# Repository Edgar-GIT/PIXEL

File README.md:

# PIXEL

**Sistema inteligente de assistência à identificação de cores** — Prova de Aptidão Profissional (PAP) — apresentação de introdução.

O PIXEL é um pequeno módulo eletrónico destacável, para acoplar a praticamente qualquer par de óculos. Ajuda pessoas com daltonismo (deficiência da visão cromática) a identificar cores e a interpretar informação visual. Tem dois modos:

- **Traffic Mode** — analisa automaticamente as imagens da câmara, deteta semáforos e o seu estado, e emite um aviso sonoro quando há uma mudança confirmada. Funciona sem comandos de voz nem botões.
- **Free Vision** — responde a perguntas por voz ("PIXEL, qual é a cor do objeto à minha frente?"), usando visão computacional e IA (Gemini).

> ⚠️ O PIXEL é um **protótipo experimental de assistência**. Não é um sistema certificado de segurança rodoviária e não decide se o utilizador pode atravessar. O utilizador deve continuar a observar o ambiente e a sinalização.

## Arquitetura

```
Óculos PIXEL (XIAO ESP32-S3 Sense, C++)  ──BLE + Wi-Fi──►  App Android (Kotlin + OpenCV)  ──HTTPS──►  Backend (Go)  ──►  Gemini API
   câmara · microfone · altifalante                          modos · deteções · voz                     API · encaminhamento
```

| Tecnologia | Responsabilidade |
|---|---|
| C++ | Firmware do ESP32-S3 |
| Kotlin | Aplicação Android |
| Go | Backend e API |
| OpenCV | Visão computacional (no telemóvel) |
| Gemini API | Interpretação de imagens e linguagem natural |
| KiCad 10 | Esquema, PCB e modelos 3D |

## Estado atual (rev. 0.1 — 22/11/2026)

| Componente | Estado |
|---|---|
| Hardware — protótipo em meia placa perfurada 35 × 50 mm (KiCad) | ✅ Desenhado; ERC/DRC sem erros; peças iniciais + divisor de tensão da bateria |
| Hardware — PCB final (KiCad) | ✅ Desenhado; ERC/DRC sem erros; **ainda não fabricado nem testado** |
| Documentação de hardware e orçamento | ✅ [`hardware/PIXEL_HARDWARE.md`](hardware/PIXEL_HARDWARE.md) · [`hardware/PIXEL_BOM.csv`](hardware/PIXEL_BOM.csv) |
| Apresentação PAP | ✅ `apresentacoes/PIXEL_PAP.pptx` + guião `apresentacoes/PIXEL_GUIAO.md` |
| Firmware, aplicação Android, backend | ⏳ Por desenvolver (fora do âmbito desta fase) |

## Estrutura do repositório

```
PIXEL/
├── README.md
├── logo.png                         ← logótipo original
├── apresentacoes/
│   ├── PIXEL_PAP.pptx               ← apresentação da PAP (editável)
│   ├── PIXEL_GUIAO.md               ← o que dizer em cada diapositivo
│   ├── assets/                      ← logótipo transparente, renders KiCad, imagens dos slides
│   └── exports/                     ← PDF da apresentação
├── hardware/
│   ├── PIXEL_HARDWARE.md            ← arquitetura, BOM, ligações, alimentação, comunicação, pendentes
│   ├── PIXEL_BOM.csv                ← lista de materiais com preços e fontes
│   ├── datasheets/                  ← datasheets consultados
│   ├── renders/                     ← protótipo (PIXEL_PROTO_*), layout e 3D da PCB final, esquemas (PDF/PNG)
│   └── kicad/
│       ├── libs/                    ← bibliotecas do projeto (Seeed OPL + modelos 3D)
│       ├── PIXEL/                   ← PCB final (54 × 24 mm) + fabrication/ (Gerbers)
│       ├── PIXEL_DEV/               ← PCB final em vista de layout (mesmo esquema)
│       ├── PIXEL_PROTO/             ← protótipo: layout final (meia placa 35 × 50 mm)
│       ├── PIXEL_PROTO_DEV/         ← protótipo: vista de ligações 70 × 50 mm
│       └── reports/                 ← relatórios ERC/DRC
└── relatorios/                      ← relatório da PAP (outra fase)
```

## Abrir os projetos KiCad

1. Instalar o **KiCad 10** (os ficheiros foram criados e verificados com o KiCad 10.0.8).
2. Abrir `hardware/kicad/PIXEL_PROTO/PIXEL_PROTO.kicad_pro` (protótipo; vista de ligações em `PIXEL_PROTO_DEV`), `hardware/kicad/PIXEL/PIXEL.kicad_pro` (PCB final) ou `hardware/kicad/PIXEL_DEV/PIXEL_DEV.kicad_pro` (layout da PCB final).
3. As bibliotecas do projeto carregam-se automaticamente, com caminhos relativos para `hardware/kicad/libs/`.

Verificação pela linha de comandos:

```bash
cd hardware/kicad/PIXEL
kicad-cli sch erc PIXEL.kicad_sch
kicad-cli pcb drc --schematic-parity PIXEL.kicad_pcb
```

## Créditos e licenças

- Símbolo, footprint e esquema de referência do XIAO ESP32-S3: [Seeed Studio OPL KiCad Library](https://github.com/Seeed-Studio/OPL_Kicad_Library) (CC BY-SA 4.0).
- Modelo 3D do XIAO ESP32-S3 Sense: Seeed Studio (pacote oficial da wiki).
- Restantes símbolos, footprints e modelos 3D: bibliotecas oficiais do KiCad.

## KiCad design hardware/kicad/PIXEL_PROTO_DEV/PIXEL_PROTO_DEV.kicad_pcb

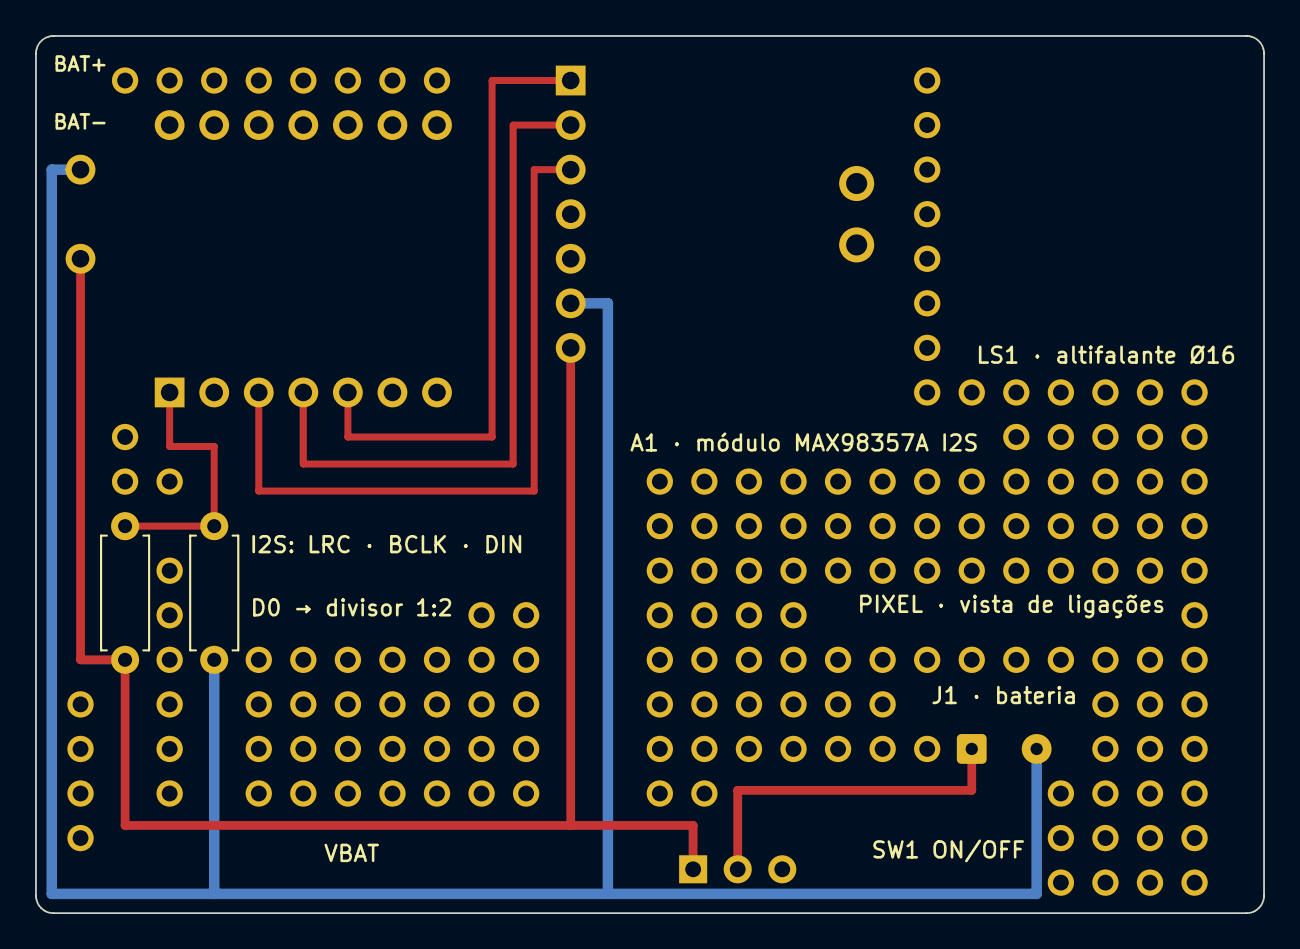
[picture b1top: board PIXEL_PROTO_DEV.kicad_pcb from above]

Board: 2 copper layers, 70.0 x 50.0 mm, 9 parts (1 on the bottom side), 7 nets.

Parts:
A1: Módulo MAX98357A I2S; Adafruit_MAX98357A_3006
J1: Fios da bateria; SolderWire-0.127sqmm_1x02_P3.7mm_D0.48mm_OD1mm
MECH1: Speaker_LD-SP-U15.5_Virtual
MECH2: LiPo_EasyLander_103040_Virtual
PERF1: Placa perfurada 70x50 mm (vista de ligações); Perfboard_70x50_P2.54mm
R1, R2: 100k; R_Axial_DIN0207_L6.3mm_D2.5mm_P7.62mm_Horizontal
SW1: ESP1010 0,5 A (ON/OFF); SW_Slide_SPDT_ESP1010_P2.54mm
U1: XIAO ESP32-S3 Sense; XIAO-ESP32-S3-Sense_Headers_BATwires

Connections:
/BAT+: J1.1, SW1.2
/I2S_BCLK: A1.2, U1.4
/I2S_DOUT: A1.3, U1.3
/I2S_LRCLK: A1.1, U1.5
/VBAT: A1.7, R1.1, SW1.1, U1.23
/VBAT_SENSE: R1.2, R2.1, U1.1
GND: A1.6, J1.2, R2.2, U1.24

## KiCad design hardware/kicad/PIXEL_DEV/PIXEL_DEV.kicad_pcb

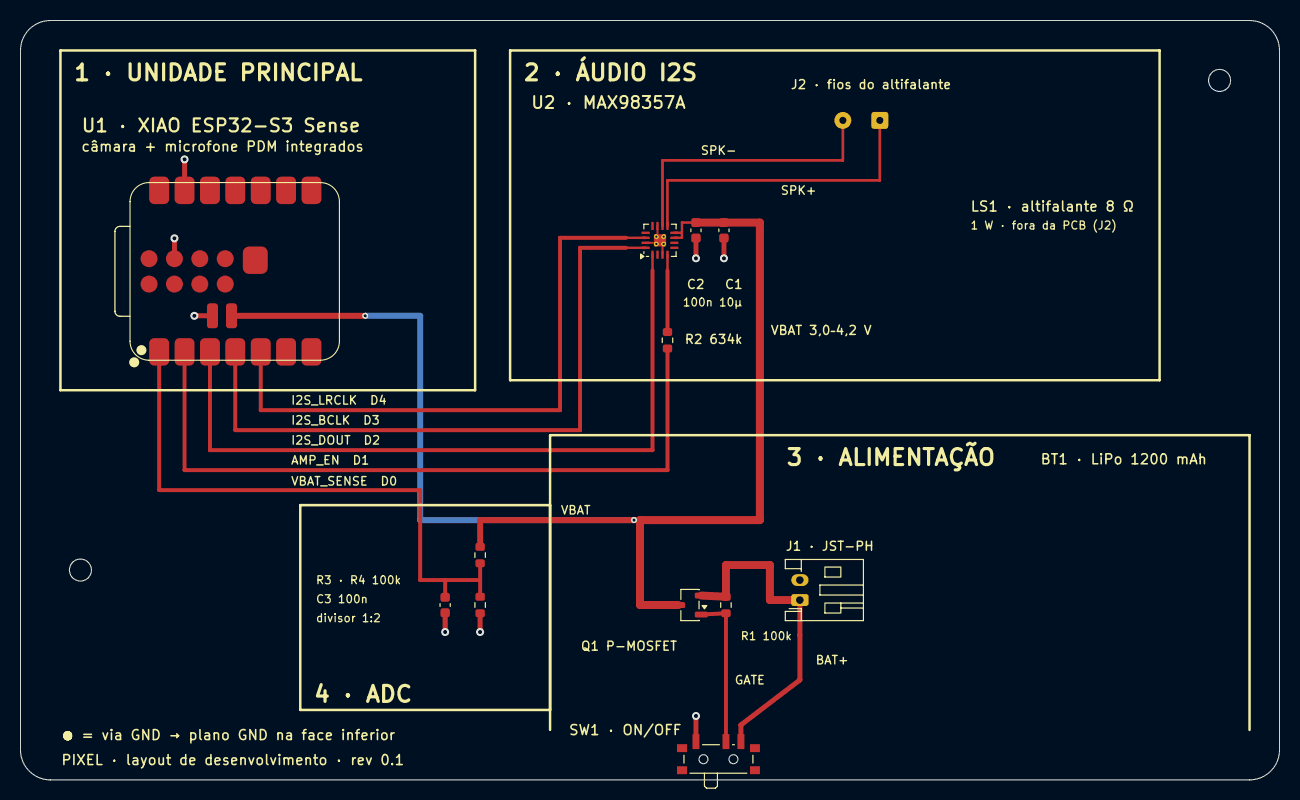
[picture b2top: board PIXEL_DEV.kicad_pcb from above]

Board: 2 copper layers, 126.0 x 76.0 mm, 17 parts (0 on the bottom side), 12 nets.

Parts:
C1: 10u; C_0603_1608Metric
C2, C3: 100n; C_0603_1608Metric
H1, H2: M2; MountingHole_2.2mm_M2
J1: JST-PH 2p (bateria); JST_PH_S2B-PH-K_1x02_P2.00mm_Horizontal
J2: Pads p/ altifalante; SolderWire-0.127sqmm_1x02_P3.7mm_D0.48mm_OD1mm
MECH1: Speaker_LD-SP-U15.5_Virtual
MECH2: LiPo_EasyLander_103040_Virtual
Q1: DMG2305UX-7; SOT-23-3
R1, R3, R4: 100k; R_0603_1608Metric
R2: 634k 1%; R_0603_1608Metric
SW1: PCM12SMTR (ON/OFF); SW_SPDT_PCM12
U1: XIAO ESP32-S3 Sense; XIAO-ESP32-S3-SMD
U2: MAX98357AETE+T; TQFN-16-1EP_3x3mm_P0.5mm_EP1.23x1.23mm_ThermalVias

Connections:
/AMP_EN: R2.1, U1.2
/AMP_SD: R2.2, U2.4
/BAT+: J1.1, Q1.2, R1.1, SW1.3
/I2S_BCLK: U1.4, U2.16
/I2S_DOUT: U1.3, U2.1
/I2S_LRCLK: U1.5, U2.14
/PWR_CTRL: Q1.1, R1.2, SW1.2
/SPK_N: J2.2, U2.10
/SPK_P: J2.1, U2.9
/VBAT: C1.1, C2.1, Q1.3, R3.1, U1.23, U2.7, U2.8
/VBAT_SENSE: C3.1, R3.2, R4.1, U1.1
GND: C1.2, C2.2, C3.2, J1.2, R4.2, SW1.1, U1.13, U1.18, U1.24, U2.3, U2.11, U2.15, U2.17
